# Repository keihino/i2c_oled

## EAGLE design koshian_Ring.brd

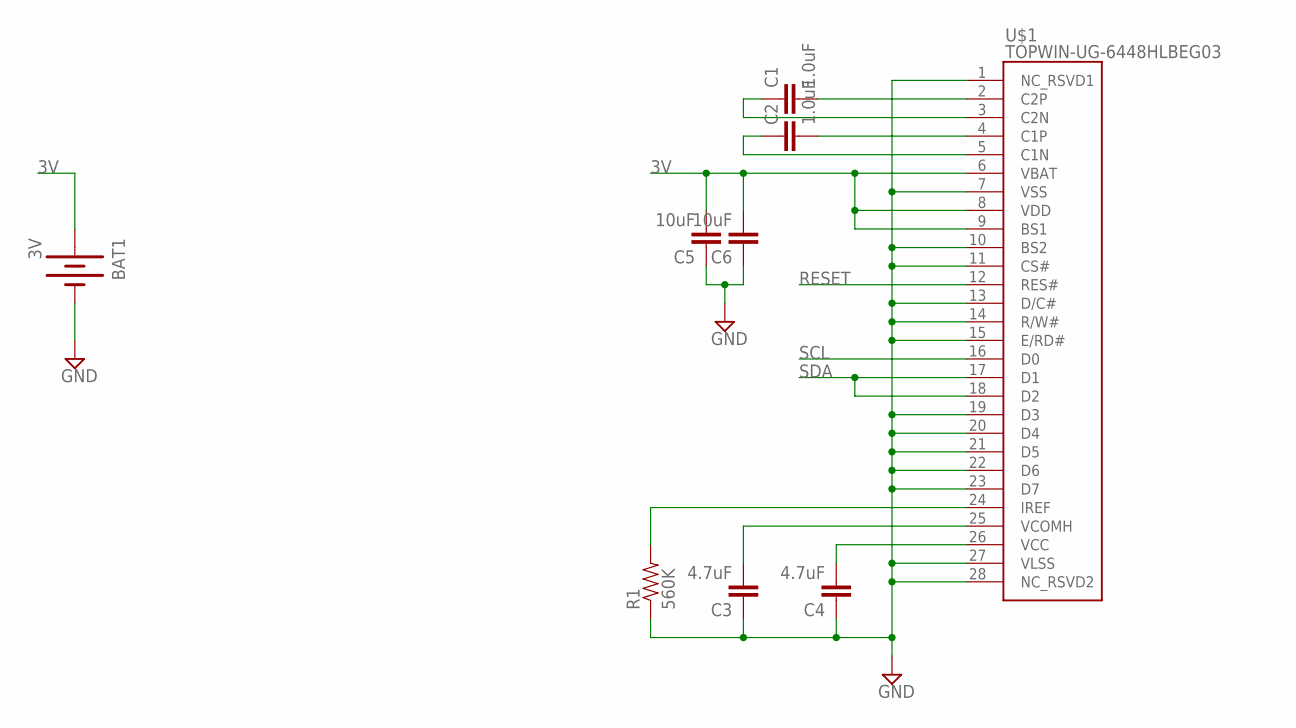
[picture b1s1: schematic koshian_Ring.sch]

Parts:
BAT1: 3V; BATTCON_20MM
C1, C2: 1.0uF; 1206-CAP
C3, C4: 4.7uF; 1206-CAP
C5, C6: 10uF; 1206-CAP
R1: 560K; 1206
U$1: TOPWIN-UG-6448HLBEG03

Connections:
3V: BAT1.1 (+), C5.2, C6.2, U$1.6 (VBAT), U$1.8 (VDD), U$1.9 (BS1)
GND: BAT1.2 (-), C3.1, C4.1, C5.1, C6.1, R1.1, U$1.1 (NC_RSVD1), U$1.7 (VSS), U$1.10 (BS2), U$1.11 (CS#), U$1.13 (D/C#), U$1.14 (R/W#), U$1.15 (E/RD#), U$1.19 (D3), U$1.20 (D4), U$1.21 (D5), U$1.22 (D6), U$1.23 (D7), U$1.27 (VLSS), U$1.28 (NC_RSVD2)
unnamed: C1.2, U$1.2 (C2P)
unnamed: C1.1, U$1.3 (C2N)
unnamed: C2.2, U$1.4 (C1P)
unnamed: C2.1, U$1.5 (C1N)
unnamed: R1.2, U$1.24 (IREF)
unnamed: C4.2, U$1.26 (VCC)
unnamed: C3.2, U$1.25 (VCOMH)
RESET: U$1.12 (RES#)
SCL: U$1.16 (D0)
SDA: U$1.17 (D1), U$1.18 (D2)

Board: 2 copper layers, 9 parts (0 on the bottom side), 10 nets, no tracks yet.

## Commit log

2016-11-02 :confetti_ball: Added .gitattributes & .gitignore files
2016-11-02 init
2016-11-02 add brd

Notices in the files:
parts and their libraries:
SparkFun-Capacitors: Licensing: Creative Commons ShareAlike 4.0 International - https://creativecommons.org/licenses/by-sa/4.0
